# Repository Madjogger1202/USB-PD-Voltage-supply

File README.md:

# USB-PD Voltage supply

<table align="center">
  <tr>
    <td>
      
    </td> 
    <td>
      
    </td>
  </tr>
</table>

# Universal Programmable Power Supply Module

A compact, network-enabled power solution designed for debugging modern semiconductor components (e.g., PCIe switches, ASICs, and multi-voltage SoCs). Replaces traditional bench power supplies with a single integrated unit featuring precise voltage control, remote accessibility, and modular expandability.

---

> [!IMPORTANT]
> Project wasn't produced and tested yet.

## Key Features

- **Dual Adjustable DC-DC Outputs**  
  0.8–22 V, 6 A per channel (TPS55289RYQR controllers)  
- **Dual Fixed 5 V Outputs**  
  3 A each (LMR16030PDDAR), one for system logic, one for LDO input  
- **Low-Noise LDO Output**  
  0.5–5 V, 3 A (TPS7A5701RTER with TPL0501-100DCNR digital potentiometer)  
- **Universal Input**  
  Accepts 5–20 V via USB-C Power Delivery (STUSB4500QTR) or barrel jack (max 21 V input)  
- **Network Control**  
  ESP32-C3-based management with secure Wi-Fi/BLE, web interface, and Telegram bot  
- **Precision Monitoring**  
  ±1% current sensing via INA180A2 and ESP32-C3 ADC  
- **Expandable I/O**  
  Integrated GPIO expander for external modules or physical control buttons  
- **PCB Stackup**  
  4-layer board designed for stable power distribution, reduced noise, and improved thermal performance. Layers include dedicated power and ground planes for enhanced signal integrity. 
---

## Technical Specifications

| **Parameter**         | **Details**                                                                 |
|------------------------|-----------------------------------------------------------------------------|
| **Input**              | USB-C PD (20 V/5 A) or 5.5×2.5 mm barrel jack (5–20 V)                      |
| **Adjustable Rails**   | 2× 0.8–22 V / 6 A (DC-DC), 1× 0.5–5 V / 3 A (LDO)                           |
| **Fixed Rails**        | 2× 5 V / 3 A (DC-DC)                                                        |
| **Control Interface**  | ESP32-C3 (Wi-Fi 4, BLE 5), REST API, web UI, Telegram bot                   |
| **Display**            | 2.0" ST7789 (320×240) TFT with real-time voltage/current monitoring         |
| **Current Sensing**    | INA180A2 amplifier with 12-bit ADC resolution                               |
| **Safety Limits**      | Input voltage ≤ 21 V; overcurrent/overvoltage protection per channel        |

---

## PCB
<div align="center">
  
  &nbsp;&nbsp;&nbsp;&nbsp;
  
  &nbsp;&nbsp;&nbsp;&nbsp;
  
</div>

## Functional diagram

## Standard Configuration

- 6× banana jack terminal pairs 
- 2.0" ST7789 color display (320×240 resolution)  
- USB-A port for peripheral connectivity  
- 12 mm illuminated push-button (power control)    

---

## Development Ecosystem

- **Schematic & PCB Design**: KiCad 9.0 (4-layer stackup)  
- **3D Modeling**: Fusion 360 
- **Firmware**: PlatformIO (Arduino)  

---

## Use Cases

- General-purpose bench power supply
- PCIe switch and high-speed interface debugging  
- Multi-rail ASIC/FPGA prototyping  
- Low-noise analog/digital mixed-signal validation  
- Automated test environments requiring remote power cycling  

---

## Documentation

  - [Schematics](USB-PD-Voltage-supply.pdf)  
  - [Interactive HTML BOM](BOM/USB-PD-Voltage-supply-Interactive-BOM.html)  
  - [3D model with case](3D/USB-PD-Voltage-supply-with-case.step)  
  - Code for PlatformIO coming soon

> **Note**: Input voltage must not exceed 21 V. Always verify load requirements before operation.

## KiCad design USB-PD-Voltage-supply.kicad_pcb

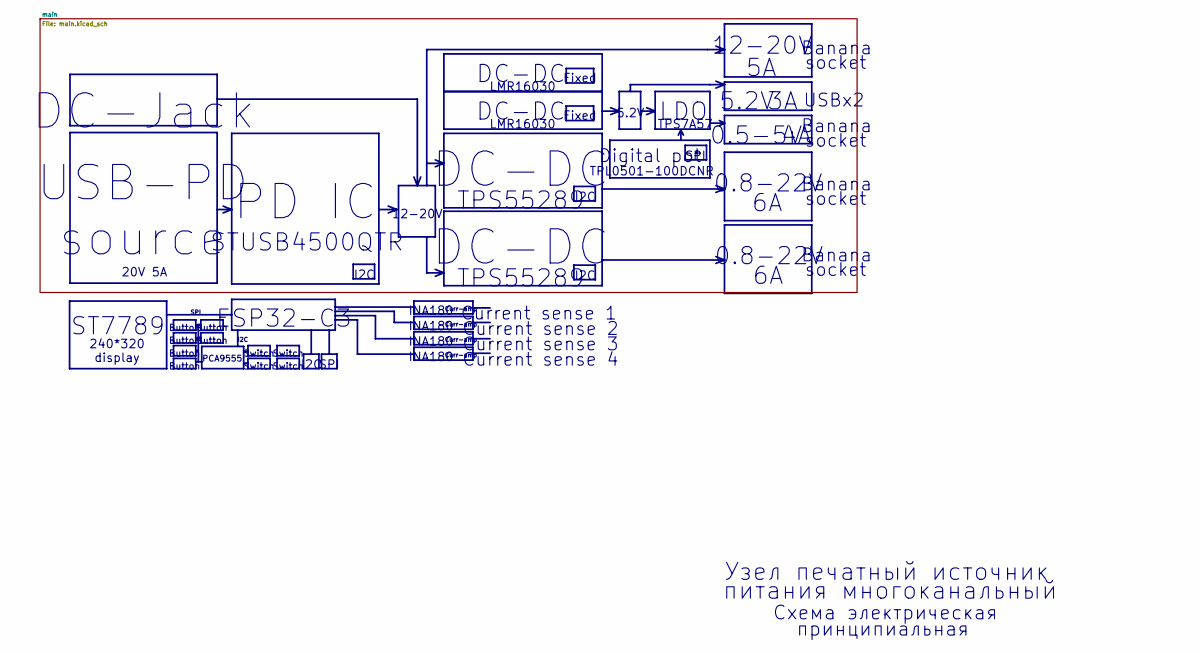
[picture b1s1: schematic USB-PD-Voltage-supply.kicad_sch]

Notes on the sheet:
Curr-amp
PD IC
питания многоканальный
TPS7A57
socket
I2C
INA180
Button
USBx2
Fixed
0.8-22V
12-20V
Banana
TPS55289
5.2V
Current sense 2
LMR16030
STUSB4500QTR
Current sense 1
LDO
SPI
240*320 display
Узел печатный источник
Digital pot
Switch
DC-DC
20V 5A
DC-Jack
USB-PD source
TPL0501-100DCNR
ST7789
PCA9555
Current sense 4
Схема электрическая
принципиальная
0.5-5V
Current sense 3
ESP32-C3

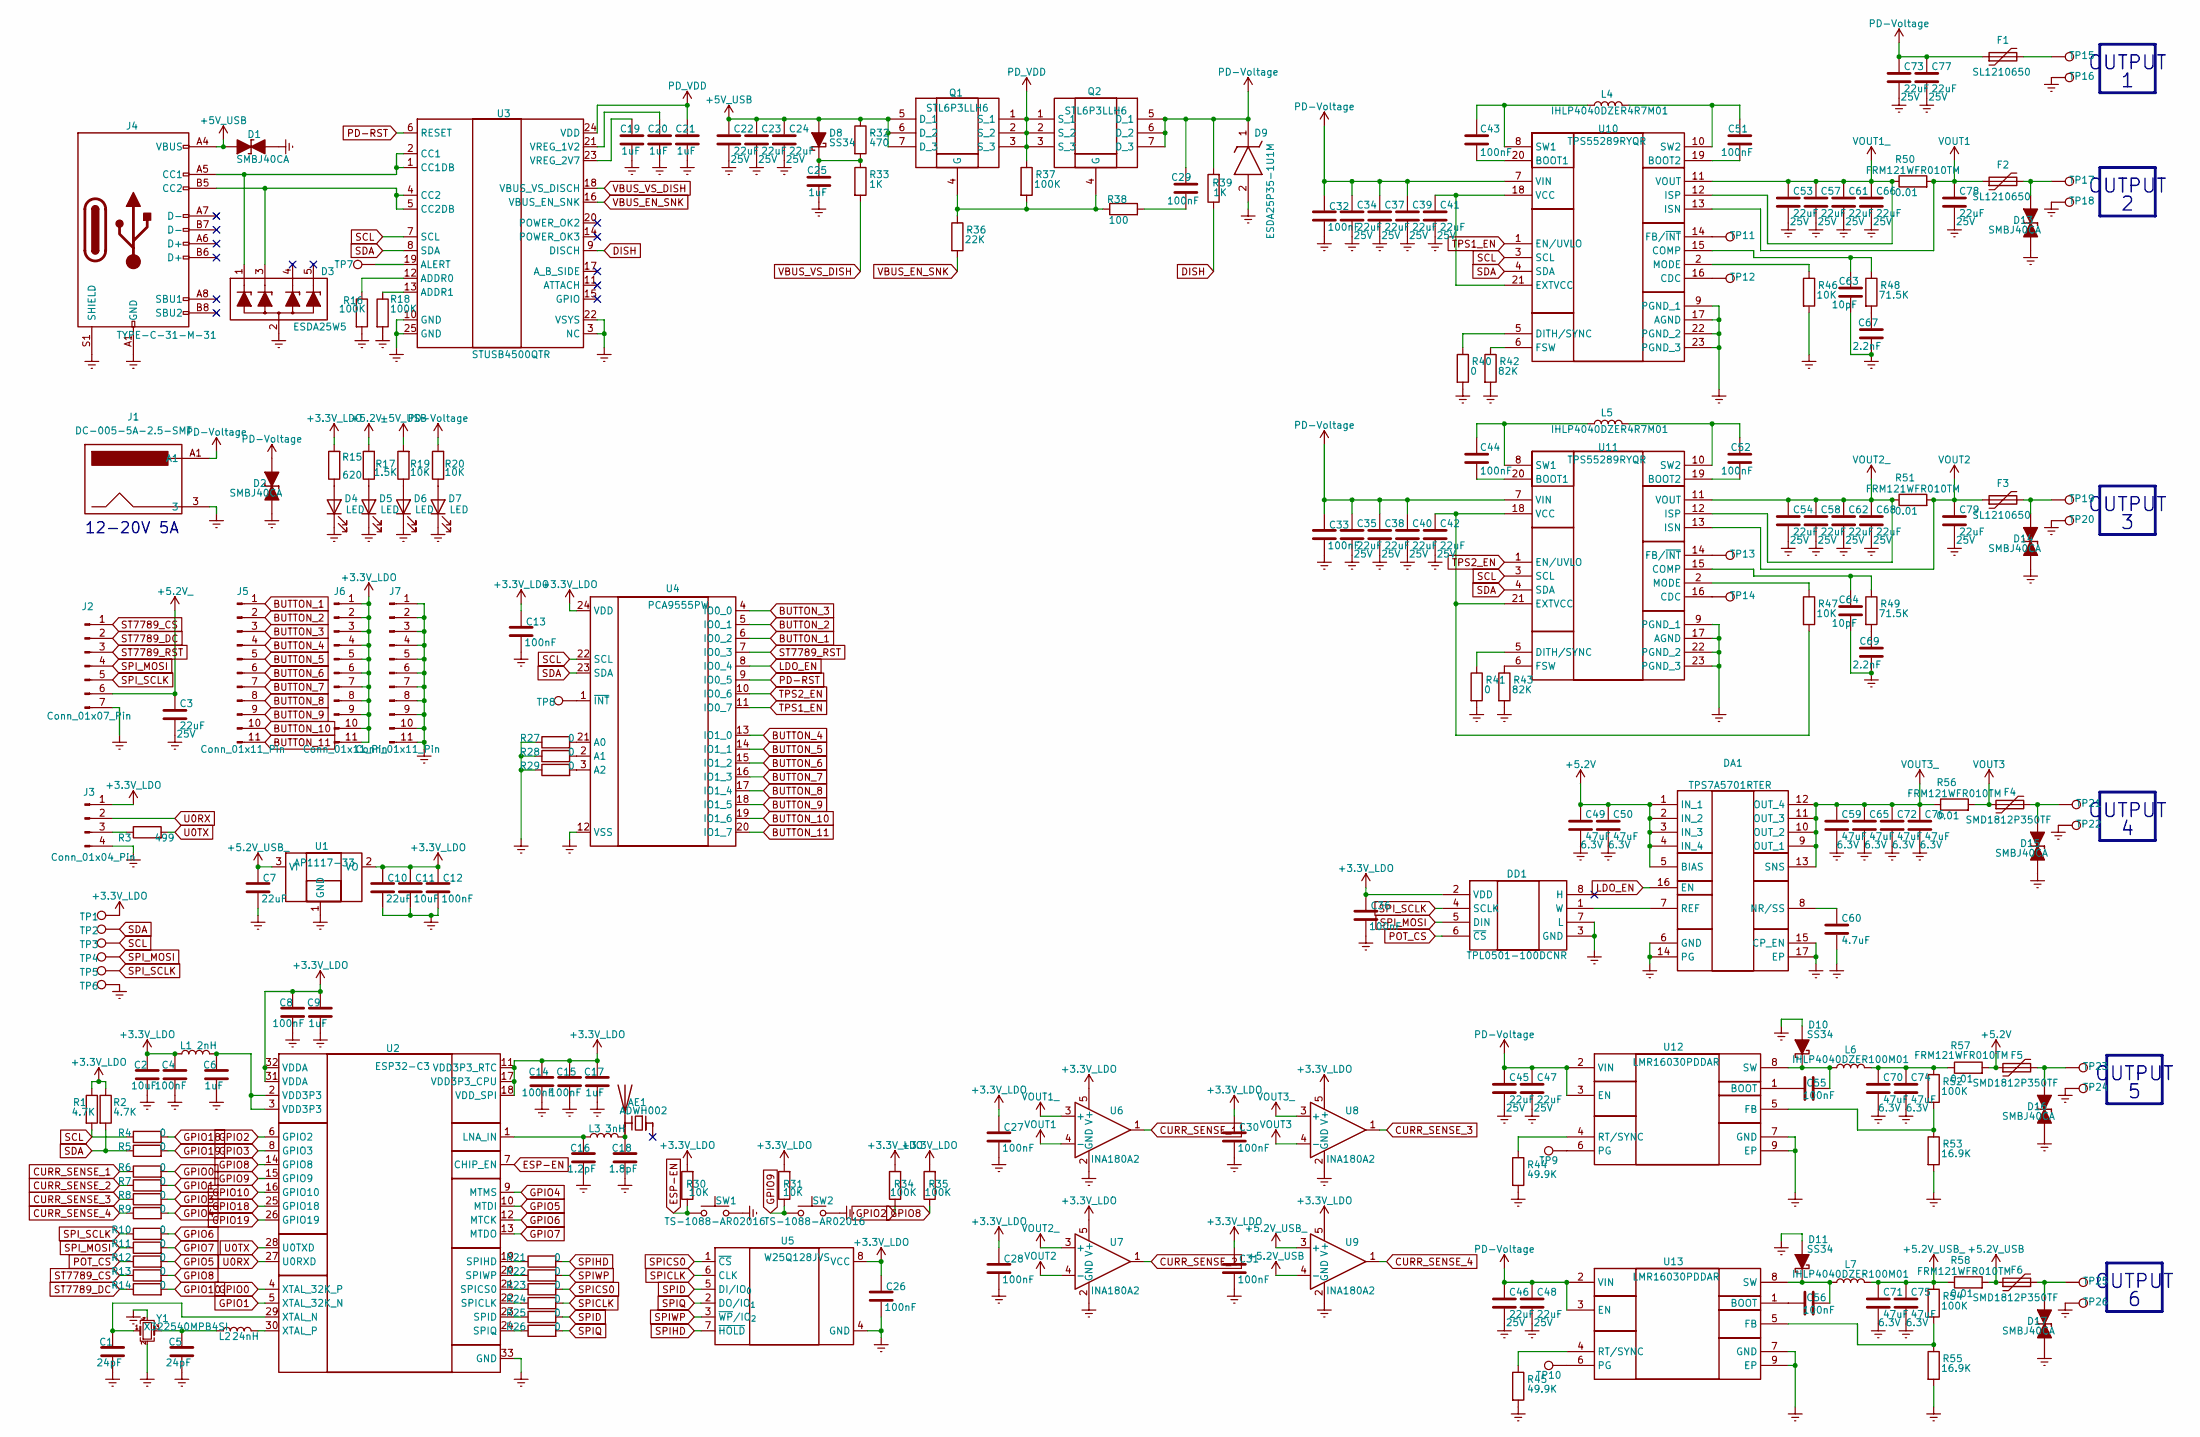
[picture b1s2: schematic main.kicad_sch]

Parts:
AE1: ADWH002; R_1206_3216Metric
C1, C5: 24pF; C_0201_0603Metric
C2, C11: 10uF; C_0402_1005Metric
C3, C22, C23, C24, C34, C35, C37, C38, C39, C40, C41, C42, C45, C46, C47, C48, C53, C54, C57, C58, C61, C62, C66, C68, C73, C77, C78, C79: 22uF; C_0805_2012Metric; Voltage 25V
C4, C8, C14, C15: 100nF; C_0201_0603Metric
C6, C9, C17: 1uF; C_0201_0603Metric
C7, C10: 22uF; C_0402_1005Metric
C12, C13, C26, C27, C28, C29, C30, C31, C32, C33, C36, C43, C44, C51, C52, C55, C56: 100nF; C_0402_1005Metric
C16: 1.2pF; C_0201_0603Metric
C18: 1.8pF; C_0201_0603Metric
C19, C20, C21, C25: 1uF; C_0402_1005Metric
C49, C50, C59, C65, C70, C71, C72, C74, C75, C76: 47uF; C_0805_2012Metric; Voltage 6.3V
C60: 4.7uF; C_0402_1005Metric; Voltage 6.3V
C63, C64: 10pF; C_0402_1005Metric
C67, C69: 2.2nF; C_0402_1005Metric
D1, D2, D13, D14, D15, D16, D17: SMBJ40CA; D_SMB_TVS
D3: ESDA25W5; SOT-353_SC-70-5
D4, D5, D6, D7: LED; LED_0402_1005Metric
D8, D10, D11: SS34; D_SMA
D9: ESDA25P35-1U1M; ESDA25P351U1M; Manufacturer_Part_Number ESDA25P35-1U1M; Mouser Part Number 511-ESDA25P35-1U1M
DA1: TPS7A5701RTER; TPS7A57; Manufacturer_Part_Number TPS7A5701RTER; Mouser Part Number 595-TPS7A5701RTER
DD1: TPL0501-100DCNR; SOT65P280X145-8N; Manufacturer_Part_Number TPL0501-100DCNR; Mouser Part Number 595-TPL0501-100DCNR
F1, F2, F3: SL1210650; Fuse_1210_3225Metric
F4, F5, F6: SMD1812P350TF; Fuse_1812_4532Metric
J1: DC-005-5A-2.5-SMT; DC-005-5A; Manufacturer_Part_Number DC-005-5A-2.5-SMT
J2: Conn_01x07_Pin; PinHeader_1x07_P1.27mm_Vertical
J3: Conn_01x04_Pin; PinSocket_1x04_P2.54mm_Vertical
J4: TYPE-C-31-M-31; USB_C_Receptacle_G-Switch_GT-USB-7010ASV
J5, J6, J7: Conn_01x11_Pin; PinHeader_1x11_P1.27mm_Vertical
L1: 2nH; L_0402_1005Metric
L2: 24nH; L_0201_0603Metric
L3: 3nH; L_0201_0603Metric
L4, L5: IHLP4040DZER4R7M01; L_APV_APH1040
L6, L7: IHLP4040DZER100M01; L_APV_APH1040
Q1, Q2: STL6P3LLH6; STL8N10F7; Manufacturer_Part_Number STL6P3LLH6; Mouser Part Number 511-STL6P3LLH6
R1, R2: 4.7K; R_0201_0603Metric
R3: 499; R_0201_0603Metric
R4, R5, R6, R7, R8, R9, R10, R11, R12, R13, R14, R21, R22, R23, R24, R25, R26, R27, R28, R29: 0; R_0201_0603Metric
R15: 620; R_0402_1005Metric
R16, R18, R37, R52, R54: 100K; R_0402_1005Metric
R17: 1.5K; R_0402_1005Metric
R19, R20, R46, R47: 10K; R_0402_1005Metric
R30, R31: 10K; R_0201_0603Metric
R32: 470; R_0402_1005Metric
R33, R39: 1K; R_0402_1005Metric
R34, R35: 100K; R_0201_0603Metric
R36: 22K; R_0402_1005Metric
R38: 100; R_0402_1005Metric
R40, R41: 0; R_0402_1005Metric
R42, R43: 82K; R_0402_1005Metric
R44, R45: 49.9K; R_0402_1005Metric
R48, R49: 71.5K; R_0402_1005Metric
R50, R51, R56, R57, R58: 0.01; R_1206_3216Metric
R53, R55: 16.9K; R_0402_1005Metric
SW1, SW2: TS-1088-AR02016; SW_SPST_B3U-1000P
TP1, TP2, TP3, TP4, TP5, TP6, TP7, TP8, TP9, TP10, TP11, TP12, TP13, TP14: TestPoint; TestPoint_Pad_D1.5mm
TP15, TP16, TP17, TP18, TP19, TP20, TP21, TP22, TP23, TP24, TP25, TP26: TestPoint; TestPoint_power
U1: AP1117-33; SOT-223-3_TabPin2
U2: ESP32-C3; QFN-32-1EP_5x5mm_P0.5mm_EP3.7x3.7mm
U3: STUSB4500QTR; QFN-24-1EP_4x4mm_P0.5mm_EP2.7x2.7mm
U4: PCA9555PW; TSSOP-24_4.4x7.8mm_P0.65mm
U5: W25Q128JVS; SOIC-8_5.3x5.3mm_P1.27mm
U6, U7, U8, U9: INA180A2; SOT-23-5
U10, U11: TPS55289RYQR; Manufacturer_Part_Number TPS55289RYQR; Mouser Part Number 595-TPS55289RYQR
U12, U13: LMR16030PDDAR; LMR16030; Manufacturer_Part_Number LMR16030SDDAR; Mouser Part Number 595-LMR16030SDDAR
Y1: X322540MPB4SI; Crystal_SMD_3225-4Pin_3.2x2.5mm

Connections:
+3.3V_LDO: C2.1, C4.1, C8.1, C9.1, C10.1, C11.1, C12.1, C13.1, C14.1, C15.1, C17.1, C26.1, C27.1, C28.1, C30.1, C31.1, C36.1, DD1.2 (VDD), J3.1, J6.1, J6.2, J6.3, J6.4, J6.5, J6.6, J6.7, J6.8, J6.9, J6.10, J6.11, L1.1, R1.1, R2.1, R15.2, R30.2, R31.2, R34.2, R35.2, TP1.1, U1.2 (VO), U2.11 (VDD3P3_RTC), U2.17 (VDD3P3_CPU), U2.18 (VDD_SPI), U2.31 (VDDA), U2.32 (VDDA), U4.24 (VDD), U5.8 (VCC), U6.5 (V+), U7.5 (V+), U8.5 (V+), U9.5 (V+)
+5.2V: C49.1, C50.1, DA1.1 (IN_1), DA1.2 (IN_2), DA1.3 (IN_3), DA1.4 (IN_4), DA1.5 (BIAS), F5.1, R57.2
+5.2V_: C3.1, J2.6, R17.2
+5.2V_USB: F6.1, R58.2, U9.4 (-)
+5.2V_USB_: C7.1, C71.1, C75.1, L7.2, R54.1, R58.1, U1.3 (VI), U9.3 (+)
+5V_USB: C22.1, C23.1, C24.1, D1.2 (A), D8.2 (A), J4.A4 (VBUS), J4.A9 (VBUS), J4.B4 (VBUS), J4.B9 (VBUS), Q1.5 (D_1), Q1.6 (D_2), Q1.7 (D_3), R19.2, R32.1
BUTTON_1: J5.1, U4.6 (IO0_2)
BUTTON_2: J5.2, U4.5 (IO0_1)
BUTTON_3: J5.3, U4.4 (IO0_0)
BUTTON_4: J5.4, U4.13 (IO1_0)
BUTTON_5: J5.5, U4.14 (IO1_1)
BUTTON_6: J5.6, U4.15 (IO1_2)
BUTTON_7: J5.7, U4.16 (IO1_3)
BUTTON_8: J5.8, U4.17 (IO1_4)
BUTTON_9: J5.9, U4.18 (IO1_5)
BUTTON_10: J5.10, U4.19 (IO1_6)
BUTTON_11: J5.11, U4.20 (IO1_7)
CURR_SENSE_1: R6.1, U6.1
CURR_SENSE_2: R7.1, U7.1
CURR_SENSE_3: R8.1, U8.1
CURR_SENSE_4: R9.1, U9.1
DISH: R39.1, U3.9 (DISCH)
ESP-EN: R30.1, SW1.1, U2.7 (CHIP_EN)
Earth: C1.2, C2.2, C3.2, C4.2, C5.2, C6.2, C7.2, C8.2, C9.2, C10.2, C11.2, C12.2, C13.2, C14.2, C15.2, C16.2, C17.2, C18.2, C19.2, C20.2, C21.2, C22.2, C23.2, C24.2, C25.2, C26.2, C27.2, C28.2, C30.2, C31.2, C32.2, C33.2, C34.2, C35.2, C36.2, C37.2, C38.2, C39.2, C40.2, C41.2, C42.2, C45.2, C46.2, C47.2, C48.2, C49.2, C50.2, C53.2, C54.2, C57.2, C58.2, C59.2, C60.2, C61.2, C62.2, C63.2, C64.2, C65.2, C66.2, C67.2, C68.2, C69.2, C70.2, C71.2, C72.2, C73.2, C74.2, C75.2, C76.2, C77.2, C78.2, C79.2, D1.1 (K), D2.1 (K), D3.2 (VN), D4.1 (K), D5.1 (K), D6.1 (K), D7.1 (K), D9.2 (A), D10.2 (A), D11.2 (A), D13.1 (K), D14.1 (K), D15.1 (K), D16.1 (K), D17.1 (K), DA1.6 (GND), DA1.14 (PG), DA1.15 (CP_EN), DA1.17 (EP), DD1.3 (GND), DD1.7 (L), J1.2, J1.3, J2.7, J3.4, J4.A1 (GND), J4.A12 (GND), J4.B1 (GND), J4.B12 (GND), J4.S1 (SHIELD), J7.1, J7.2, J7.3, J7.4, J7.5, J7.6, J7.7, J7.8, J7.9, J7.10, J7.11, R16.2, R18.2, R27.1, R28.1, R29.1, R40.2, R41.2, R42.2, R43.2, R44.2, R45.2, R46.2, R53.2, R55.2, SW1.2, SW2.2, TP6.1, TP16.1, TP18.1, TP20.1, TP22.1, TP24.1, TP26.1, U1.1 (GND), U2.33 (GND), U3.3 (NC), U3.10 (GND), U3.22 (VSYS), U3.25 (GND), U4.12 (VSS), U5.4 (GND), U6.2 (GND), U7.2 (GND), U8.2 (GND), U9.2 (GND), U10.9 (PGND_1), U10.17 (AGND), U10.22 (PGND_2), U10.23 (PGND_3), U11.9 (PGND_1), U11.17 (AGND), U11.22 (PGND_2), U11.23 (PGND_3), U12.7 (GND), U12.9 (EP), U13.7 (GND), U13.9 (EP), Y1.2, Y1.4
GPIO0: R6.2, U2.4 (XTAL_32K_P)
GPIO1: R7.2, U2.5 (XTAL_32K_N)
GPIO2: R34.1, U2.6 (GPIO2)
GPIO3: R8.2, U2.8 (GPIO3)
GPIO4: R9.2, U2.9 (MTMS)
GPIO5: R12.2, U2.10 (MTDI)
GPIO6: R10.2, U2.12 (MTCK)
GPIO7: R11.2, U2.13 (MTDO)
GPIO8: R13.2, R35.1, U2.14 (GPIO8)
GPIO9: R31.1, SW2.1, U2.15 (GPIO9)
GPIO10: R14.2, U2.16 (GPIO10)
GPIO18: R4.2, U2.25 (GPIO18)
GPIO19: R5.2, U2.26 (GPIO19)
LDO_EN: DA1.16 (EN), U4.8 (IO0_4)
unnamed: AE1.2 (PCB_Trace), C18.1, L3.2
unnamed: C5.1, L2.1, Y1.3
unnamed: C6.1, L1.2, U2.2 (VDD3P3), U2.3 (VDD3P3)
unnamed: C29.2, R38.2
unnamed: C67.1, R48.2
unnamed: C69.1, R49.2
unnamed: C70.1, C74.1, L6.2, R52.1, R57.1
unnamed: D3.1 (L1), J4.A5 (CC1), U3.1 (CC1DB), U3.2 (CC1)
unnamed: D3.3 (L2), J4.B5 (CC2), U3.4 (CC2), U3.5 (CC2DB)
unnamed: D4.2 (A), R15.1
unnamed: D5.2 (A), R17.1
unnamed: D6.2 (A), R19.1
unnamed: D7.2 (A), R20.1
unnamed: C25.1, D8.1 (K), R32.2, R33.1
unnamed: C55.2, D10.1 (K), L6.1, U12.8 (SW)
unnamed: C56.2, D11.1 (K), L7.1, U13.8 (SW)
unnamed: D13.2 (A), F2.2, TP17.1
unnamed: D14.2 (A), F3.2, TP19.1
unnamed: D15.2 (A), F4.2, TP21.1
unnamed: D16.2 (A), F5.2, TP23.1
unnamed: D17.2 (A), F6.2, TP25.1
unnamed: C60.1, DA1.8 (NR/SS)
unnamed: DA1.7 (REF), DD1.1 (W)
unnamed: F1.2, TP15.1
unnamed: J3.3, R3.1
unnamed: Q1.4 (G), Q2.4 (G), R36.1, R37.2, R38.1
unnamed: C16.1, L3.1, U2.1 (LNA_IN)
unnamed: R24.1, U2.22 (SPICLK)
unnamed: R23.1, U2.21 (SPICS0)
unnamed: R25.1, U2.23 (SPID)
unnamed: R21.1, U2.19 (SPIHD)
unnamed: R26.1, U2.24 (SPIQ)
unnamed: R22.1, U2.20 (SPIWP)
unnamed: C1.1, U2.29 (XTAL_N), Y1.1
unnamed: L2.2, U2.30 (XTAL_P)
unnamed: R16.1, U3.12 (ADDR0)
unnamed: R18.1, U3.13 (ADDR1)
unnamed: TP7.1, U3.19 (ALERT)
unnamed: C20.1, U3.21 (VREG_1V2)
unnamed: C19.1, U3.23 (VREG_2V7)
unnamed: R27.2, U4.21 (A0)
unnamed: R28.2, U4.2 (A1)
unnamed: R29.2, U4.3 (A2)
unnamed: TP8.1, U4.1 (~INT)
unnamed: C43.2, U10.20 (BOOT1)
unnamed: C51.2, U10.19 (BOOT2)
unnamed: TP12.1, U10.16 (CDC)
unnamed: C63.1, R48.1, U10.15 (COMP)
unnamed: R40.1, U10.5 (DITH/SYNC)
unnamed: C41.1, U10.18 (VCC), U10.21 (EXTVCC)
unnamed: TP11.1, U10.14 (FB/~INT)
unnamed: R42.1, U10.6 (FSW)
unnamed: R46.1, U10.2 (MODE)
unnamed: C43.1, L4.1, U10.8 (SW1)
unnamed: C51.1, L4.2, U10.10 (SW2)
unnamed: C44.2, U11.20 (BOOT1)
unnamed: C52.2, U11.19 (BOOT2)
unnamed: TP14.1, U11.16 (CDC)
unnamed: C64.1, R49.1, U11.15 (COMP)
unnamed: R41.1, U11.5 (DITH/SYNC)
unnamed: C42.1, R47.2, U11.18 (VCC), U11.21 (EXTVCC)
unnamed: TP13.1, U11.14 (FB/~INT)
unnamed: R43.1, U11.6 (FSW)
unnamed: R47.1, U11.2 (MODE)
unnamed: C44.1, L5.1, U11.8 (SW1)
unnamed: C52.1, L5.2, U11.10 (SW2)
unnamed: C55.1, U12.1 (BOOT)
unnamed: R52.2, R53.1, U12.5 (FB)
unnamed: TP9.1, U12.6 (PG)
unnamed: R44.1, U12.4 (RT/SYNC)
unnamed: C56.1, U13.1 (BOOT)
unnamed: R54.2, R55.1, U13.5 (FB)
unnamed: TP10.1, U13.6 (PG)
unnamed: R45.1, U13.4 (RT/SYNC)
PD-RST: U3.6 (RESET), U4.9 (IO0_5)
PD-Voltage: C29.1, C32.1, C33.1, C34.1, C35.1, C37.1, C38.1, C39.1, C40.1, C45.1, C46.1, C47.1, C48.1, C73.1, C77.1, D2.2 (A), D9.1 (K), F1.1, J1.A1, J1.B1, Q2.5 (D_1), Q2.6 (D_2), Q2.7 (D_3), R20.2, R39.2, U10.7 (VIN), U11.7 (VIN), U12.2 (VIN), U12.3 (EN), U13.2 (VIN), U13.3 (EN)
PD_VDD: C21.1, Q1.1 (S_1), Q1.2 (S_2), Q1.3 (S_3), Q2.1 (S_1), Q2.2 (S_2), Q2.3 (S_3), R37.1, U3.24 (VDD)
POT_CS: DD1.6 (~CS), R12.1
SCL: R1.2, R4.1, TP3.1, U3.7 (SCL), U4.22 (SCL), U10.3 (SCL), U11.3 (SCL)
SDA: R2.2, R5.1, TP2.1, U3.8 (SDA), U4.23 (SDA), U10.4 (SDA), U11.4 (SDA)
SPICLK: R24.2, U5.6 (CLK)
SPICS0: R23.2, U5.1 (~CS)
SPID: R25.2, U5.5 (DI/IO_{0})
SPIHD: R21.2, U5.7 (~HOLD)
SPIQ: R26.2, U5.2 (DO/IO_{1})
SPIWP: R22.2, U5.3 (~WP/IO_{2})
SPI_MOSI: DD1.5 (DIN), J2.4, R11.1, TP4.1
SPI_SCLK: DD1.4 (SCLK), J2.5, R10.1, TP5.1
ST7789_CS: J2.1, R13.1
ST7789_DC: J2.2, R14.1
ST7789_RST: J2.3, U4.7 (IO0_3)
TPS1_EN: U4.11 (IO0_7), U10.1 (EN/UVLO)
TPS2_EN: U4.10 (IO0_6), U11.1 (EN/UVLO)
U0RX: J3.2, U2.27 (U0RXD)
U0TX: R3.2, U2.28 (U0TXD)
VBUS_EN_SNK: R36.2, U3.16 (VBUS_EN_SNK)
VBUS_VS_DISH: R33.2, U3.18 (VBUS_VS_DISCH)
VOUT1: C78.1, F2.1, R50.2, U6.4 (-), U10.13 (ISN)
VOUT1_: C53.1, C57.1, C61.1, C66.1, R50.1, U6.3 (+), U10.11 (VOUT), U10.12 (ISP)
VOUT2: C79.1, F3.1, R51.2, U7.4 (-), U11.13 (ISN)
VOUT2_: C54.1, C58.1, C62.1, C68.1, R51.1, U7.3 (+), U11.11 (VOUT), U11.12 (ISP)
VOUT3: F4.1, R56.2, U8.4 (-)
VOUT3_: C59.1, C65.1, C72.1, C76.1, DA1.9 (OUT_1), DA1.10 (OUT_2), DA1.11 (OUT_3), DA1.12 (OUT_4), DA1.13 (SNS), R56.1, U8.3 (+)

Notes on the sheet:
OUTPUT
12-20V 5A

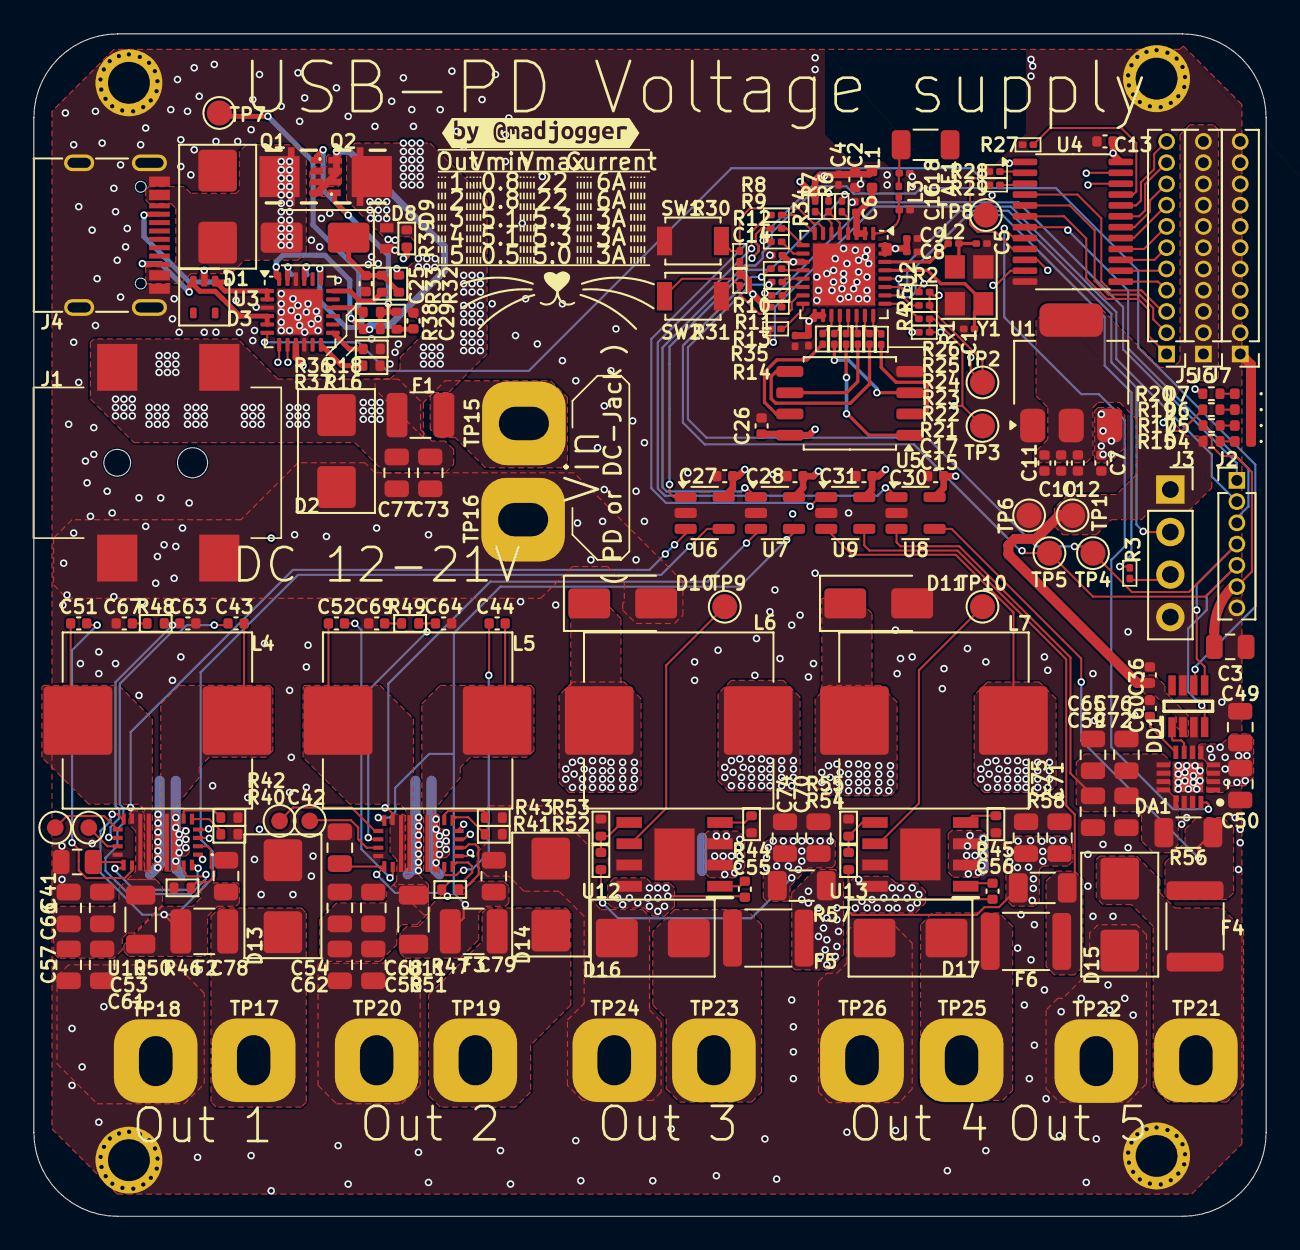
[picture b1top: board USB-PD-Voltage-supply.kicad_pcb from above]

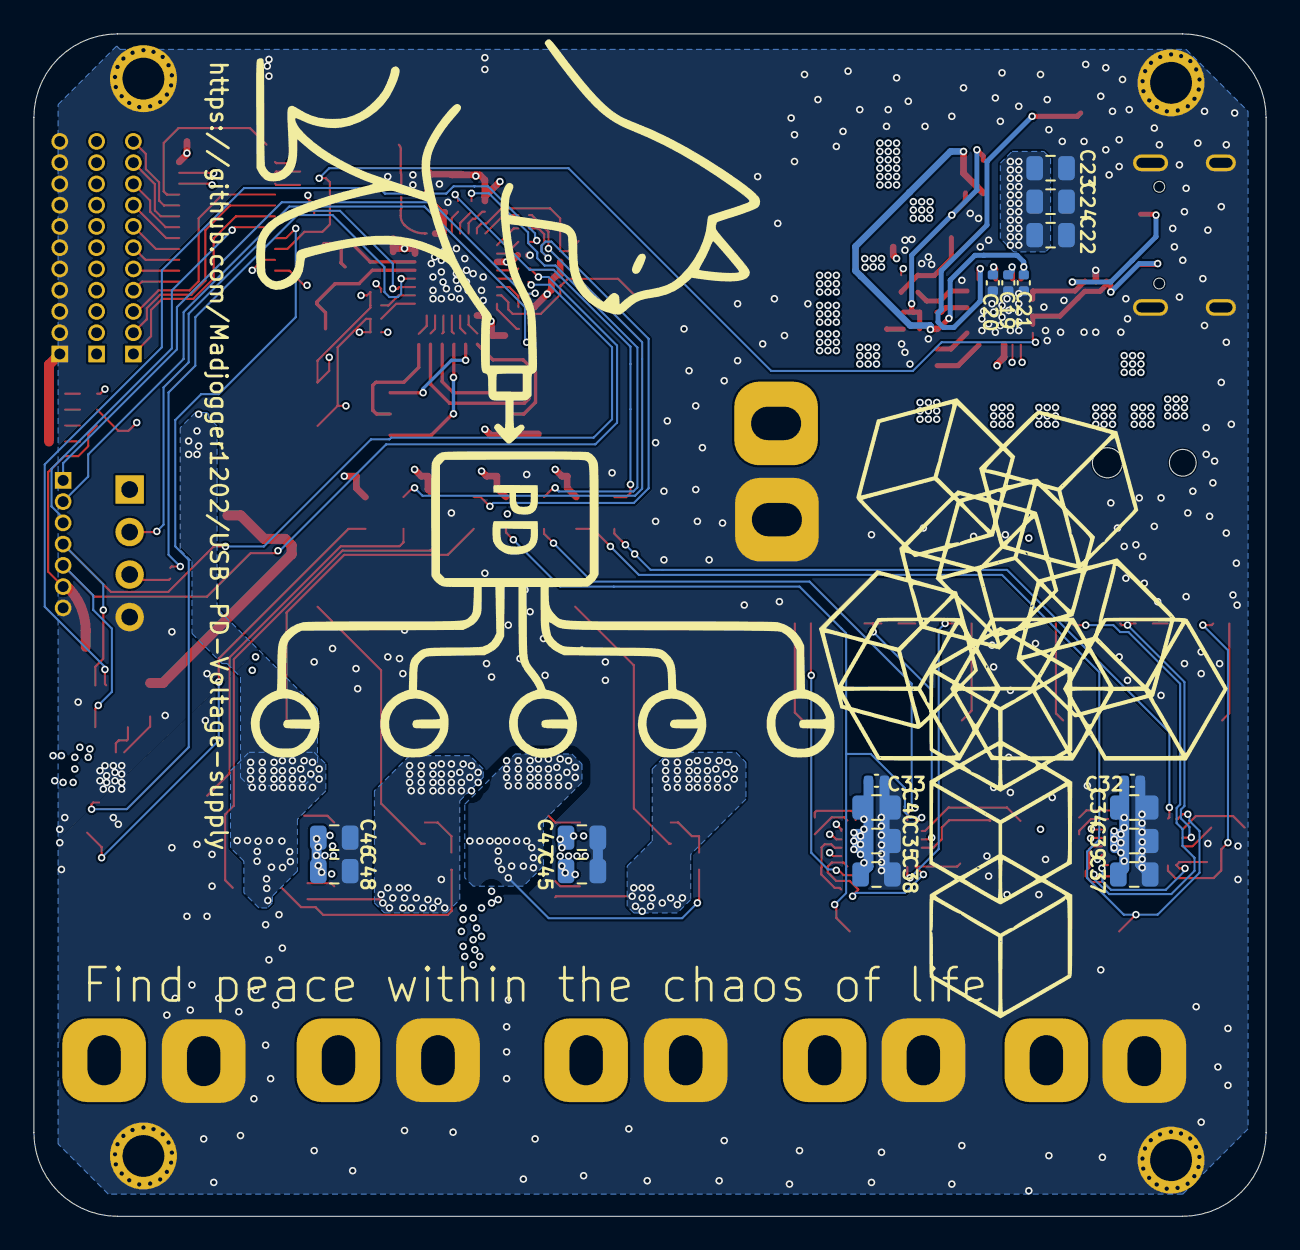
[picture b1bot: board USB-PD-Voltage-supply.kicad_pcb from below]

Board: 4 copper layers, 73.6 x 70.6 mm, 221 parts (18 on the bottom side), 141 nets.

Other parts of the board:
kibuzzard-689E2C41: G***; kibuzzard-689E2C41

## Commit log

2025-08-07 Начало работы над проектом, готова структурная схема, подобраны компоненты Добавлены необходимые библиотеки
2025-08-10 Почти завершённая схема
2025-08-11 Schematics done
2025-08-11 upd library + PCB created
2025-08-11 Added JLCPCB BOM + placed main components on PCB to form a prototype
2025-08-13 Few changes
2025-08-13 Finished components placement + silkscreen placement Reviewed schematics, changed outline Ready for tracing
2025-08-14 power poligons partly done
2025-08-14 Finished rev0
2025-08-14 Added 3D model
2025-08-15 Finished structure and manufacturing files
2025-08-15 Added README
2025-08-15 upd README
2025-08-18 PCB upd for DFM checking and manufacturing
2025-08-25 added simulation data for CST + design update ( no important changes )
